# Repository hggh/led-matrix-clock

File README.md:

# dot matrix display clock

reto dot matrix clock with LiteOn LTP-305 with three IS31FL3730

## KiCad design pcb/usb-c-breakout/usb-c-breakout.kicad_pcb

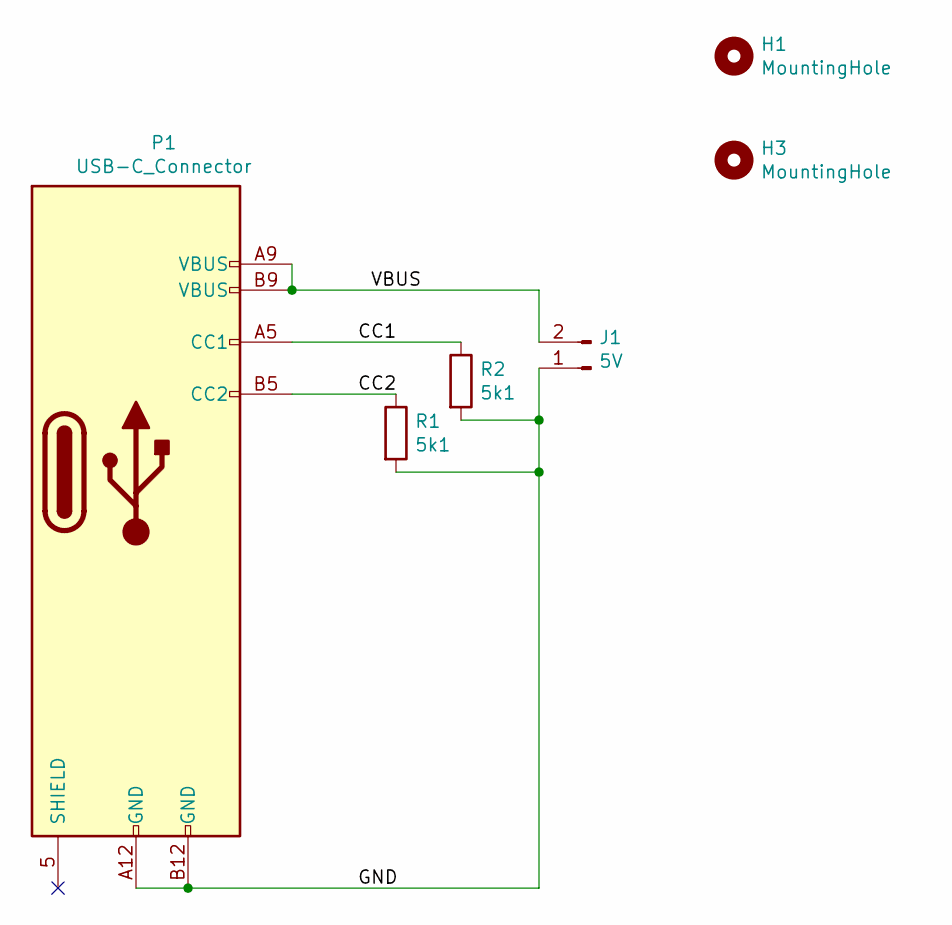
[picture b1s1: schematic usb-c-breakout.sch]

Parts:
H1, H3: MountingHole; MountingHole_2.2mm_M2
J1: 5V; PinHeader_1x02_P2.00mm_Vertical
P1: USB-C_Connector; USB-C Connector
R1, R2: 5k1; R_0805_2012Metric

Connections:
/CC1: P1.A5 (CC1), R2.1
/CC2: P1.B5 (CC2), R1.1
/GND: J1.1, P1.A12 (GND), P1.B12 (GND), R1.2, R2.2
/VBUS: J1.2, P1.A9 (VBUS), P1.B9 (VBUS)

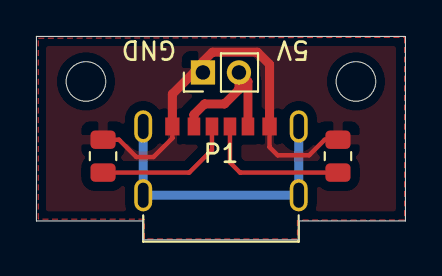
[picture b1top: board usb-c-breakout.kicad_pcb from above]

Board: 2 copper layers, 20.5 x 11.3 mm, 6 parts (0 on the bottom side), 4 nets.

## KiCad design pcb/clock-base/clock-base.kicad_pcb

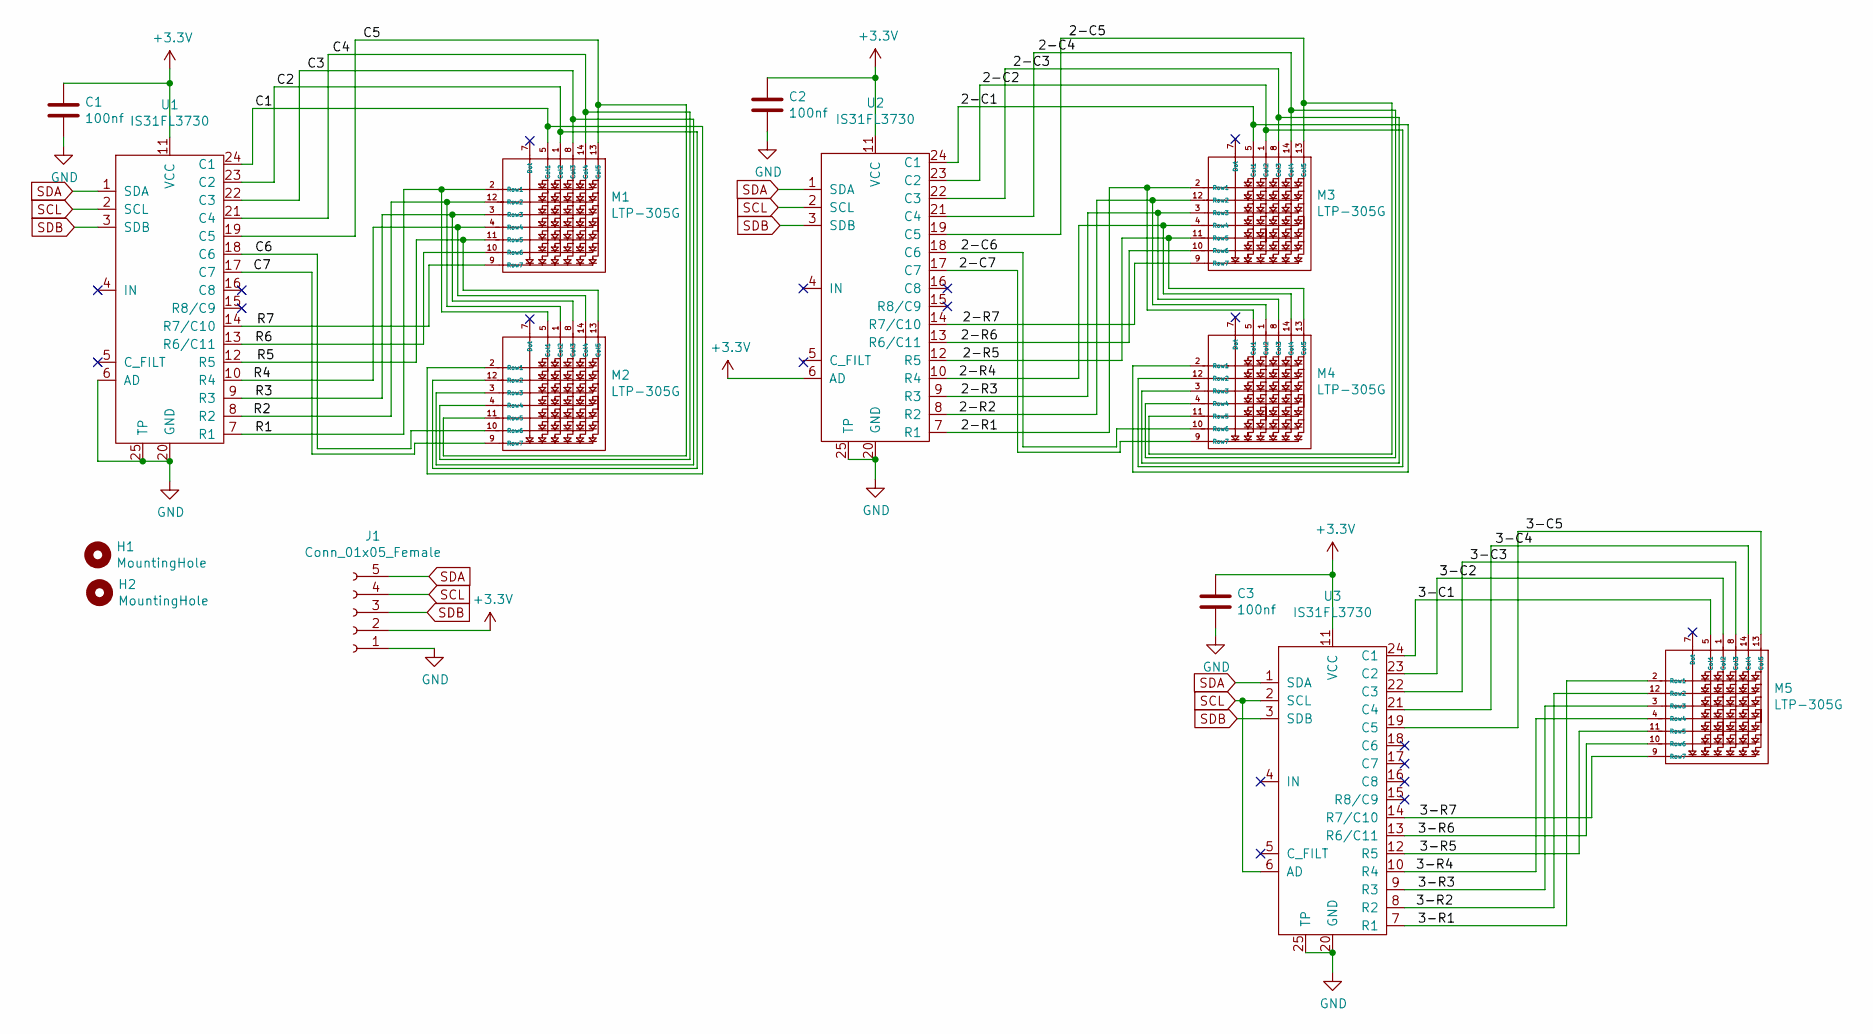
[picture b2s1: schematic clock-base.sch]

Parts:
C1, C2, C3: 100nf; C_0805_2012Metric
H1, H2: MountingHole; MountingHole_3.2mm_M3
J1: Conn_01x05_Female; PinHeader_1x05_P2.54mm_Vertical
M1, M2, M3, M4, M5: LTP-305G
U1, U2, U3: IS31FL3730; QFN-24-1EP_4x4mm_P0.5mm_EP2.6x2.6mm

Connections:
+3V3: C1.1, C2.1, C3.1, J1.2, U1.11 (VCC), U2.6 (AD), U2.11 (VCC), U3.11 (VCC)
/2-C1: M3.5 (Col1), M4.2 (Row1), U2.24 (C1)
/2-C2: M3.1 (Col2), M4.12 (Row2), U2.23 (C2)
/2-C3: M3.8 (Col3), M4.3 (Row3), U2.22 (C3)
/2-C4: M3.14 (Col4), M4.4 (Row4), U2.21 (C4)
/2-C5: M3.13 (Col5), M4.11 (Row5), U2.19 (C5)
/2-C6: M4.10 (Row6), U2.18 (C6)
/2-C7: M4.9 (Row7), U2.17 (C7)
/2-R1: M3.2 (Row1), M4.5 (Col1), U2.7 (R1)
/2-R2: M3.12 (Row2), M4.1 (Col2), U2.8 (R2)
/2-R3: M3.3 (Row3), M4.8 (Col3), U2.9 (R3)
/2-R4: M3.4 (Row4), M4.14 (Col4), U2.10 (R4)
/2-R5: M3.11 (Row5), M4.13 (Col5), U2.12 (R5)
/2-R6: M3.10 (Row6), U2.13 (R6/C11)
/2-R7: M3.9 (Row7), U2.14 (R7/C10)
/3-C1: M5.5 (Col1), U3.24 (C1)
/3-C2: M5.1 (Col2), U3.23 (C2)
/3-C3: M5.8 (Col3), U3.22 (C3)
/3-C4: M5.14 (Col4), U3.21 (C4)
/3-C5: M5.13 (Col5), U3.19 (C5)
/3-R1: M5.2 (Row1), U3.7 (R1)
/3-R2: M5.12 (Row2), U3.8 (R2)
/3-R3: M5.3 (Row3), U3.9 (R3)
/3-R4: M5.4 (Row4), U3.10 (R4)
/3-R5: M5.11 (Row5), U3.12 (R5)
/3-R6: M5.10 (Row6), U3.13 (R6/C11)
/3-R7: M5.9 (Row7), U3.14 (R7/C10)
/C1: M1.5 (Col1), M2.2 (Row1), U1.24 (C1)
/C2: M1.1 (Col2), M2.12 (Row2), U1.23 (C2)
/C3: M1.8 (Col3), M2.3 (Row3), U1.22 (C3)
/C4: M1.14 (Col4), M2.4 (Row4), U1.21 (C4)
/C5: M1.13 (Col5), M2.11 (Row5), U1.19 (C5)
/C6: M2.10 (Row6), U1.18 (C6)
/C7: M2.9 (Row7), U1.17 (C7)
/R1: M1.2 (Row1), M2.5 (Col1), U1.7 (R1)
/R2: M1.12 (Row2), M2.1 (Col2), U1.8 (R2)
/R3: M1.3 (Row3), M2.8 (Col3), U1.9 (R3)
/R4: M1.4 (Row4), M2.14 (Col4), U1.10 (R4)
/R5: M1.11 (Row5), M2.13 (Col5), U1.12 (R5)
/R6: M1.10 (Row6), U1.13 (R6/C11)
/R7: M1.9 (Row7), U1.14 (R7/C10)
GND: C1.2, C2.2, C3.2, J1.1, U1.6 (AD), U1.20 (GND), U1.25 (TP), U2.20 (GND), U2.25 (TP), U3.20 (GND), U3.25 (TP)
SCL: J1.4, U1.2 (SCL), U2.2 (SCL), U3.2 (SCL), U3.6 (AD)
SDA: J1.5, U1.1 (SDA), U2.1 (SDA), U3.1 (SDA)
SDB: J1.3, U1.3 (SDB), U2.3 (SDB), U3.3 (SDB)

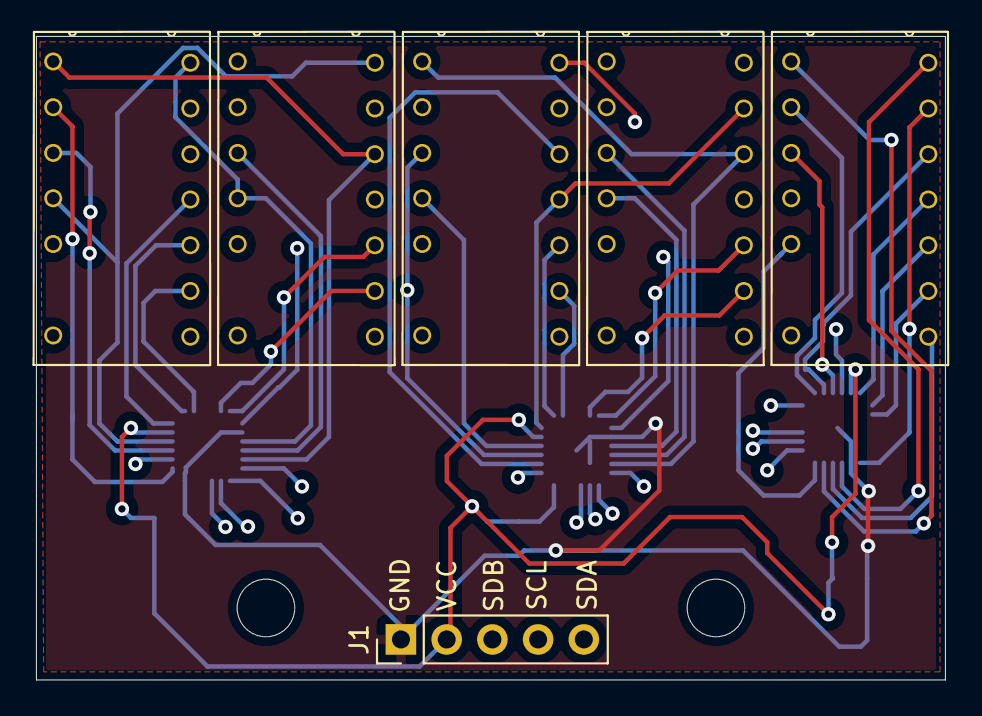
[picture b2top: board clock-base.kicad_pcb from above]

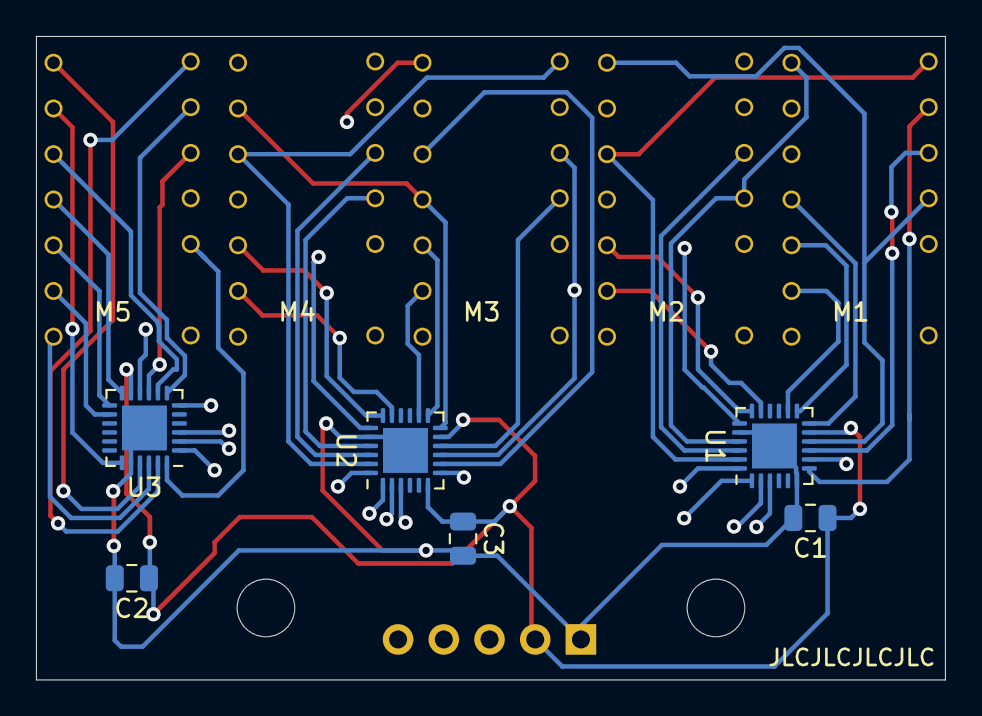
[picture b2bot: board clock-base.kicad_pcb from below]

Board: 4 copper layers, 50.5 x 35.8 mm, 14 parts (6 on the bottom side), 45 nets.

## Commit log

2021-09-22 ordered version
2021-10-07 add numbers and pio files
2021-10-08 update chars
2021-10-10 basic esp32 clock code
2021-10-10 add pin mapping on esp32
2021-10-11 add case 1. version
2021-10-11 update to case
2021-10-15 add esp8266 support
2021-10-15 updated case
2021-10-21 add holder - needs testing
2021-10-22 add blank, update colon, add second blink
2021-12-02 add usb-c breakout
2022-01-11 add case for USB-C breakout
2022-01-11 update stl
2022-02-08 update case to fit pcb
2022-02-11 add case pic
